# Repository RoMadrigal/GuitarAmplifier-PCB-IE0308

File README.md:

# GuitarAmplifier-PCB-IE0308

Repositorio para el proyecto final del curso IE0308 sobre el diseño de una PCB de un amplificador para guitarra. Contiene el circuito esquemático, el diseño de la PCB en *KiCad* y documentación sobre los componentes a utilizar, el procedimiento de diseño y otros detalles. 

Este repositorio y sus contenidos fueron diseñados durante el curso IE0308 durante el periodo I-2025 por los siguientes integrantes del equipo:

<div align="center">

|        **Integrantes**      | **Carné** | **Correo electrónico**|
|:---------------------------:|:---------:|:---------------------:|
|    Anthony Calvo García     |   C11433  |  anthonycalvo50@gmail.com |
|   Rodrigo Madrigal Montes   |   C24458  | rmadrigalmontes@gmail.com |

</div>

## Agradecimientos a PCBWay

Queremos expresar nuestro agradecimiento a **PCBWay** por su colaboración y apoyo en la fabricación de nuestras PCBs. La calidad de las placas recibidas, tanto en precisión de fabricación como en acabados, fue sobresaliente. Todo el proceso desde la carga de archivos hasta la recepción del paquete fue ágil, transparente y eficiente. 

Además siempre estuvieron disponibles para cualquier consulta, para asegurarse de que todo saliera según lo planeado, lo cual nos brindó mucho soporte y seguridad durante todo el proceso de pedido.

### PCB ensamblada

Una vez recibidas las placas de **PCBWay**, se procedió con el ensamblaje manual de todos los componentes. A continuación se muestran imágenes del resultado final:

<div align="center">

|  |
|:--:|
| *PCB ensamblada - sin los componentes externos conectados* |

</div>

<div align="center">

|  |
|:--:|
| *PCB ensamblada - con los componentes externos conectados* |

</div>

### Demostración de funcionamiento

A continuación, se presentan vídeos demostrativos del amplificador montado, funcionando correctamente tanto con una guitarra eléctrica como con un teléfono:

<p align="center">
  
  <br/>
  <em>Demostración del amplificador conectado a una guitarra eléctrica</em>
</p>

<p align="center">
  
  <br/>
  <em>Demostración del amplificador reproduciendo audio desde un teléfono</em>
</p>

Gracias a su servicio confiable y de altísima calidad, logramos ensamblar y probar con éxito nuestro amplificador, cumpliendo los objetivos del proyecto. Recomendamos sus servicios para estudiantes, profesionales y cualquier persona interesada en manufacturar PCBs de alta calidad. Más información en [pcbway.com](https://www.pcbway.com).

## Organización y contenido de los directorios 

Este repositorio contiene dos directorios principales, cuyos contenidos son:

- `kicad_project`: Contiene los archivos del esquemático, PCB y la configuarción del proyecto
    - `GuitarAmplifier.kicad_pcb`
    - `GuitarAmplifier.kicad_pro`
    - `GuitarAmplifier.kicad_sch`

- `outputs`: Contiene todos los archivos de salida de *KiCad*

Si se desea utilizar este diseño y manufacturarlo por medio de un fabricante se deben comprimir los archivos incluidos en la carpeta `outputs` en un archivo `.zip` y este se puede cargar en la página del fabricante para ordenar la fabricación de la PCB.

## Circuito base

El circuito completo del que partimos para diseñar la PCB fue primeramente fue armado y simulado en el simulador *Tina-TI*:

<div align="center">

|  |
|:--:|
| *Circuto completo del diseño* |

</div>

> [!NOTE]
> La documentación detallada de funcionamiento de cada etapa del circuito, elección de componentes, y consideraciones de diseño está disponible en la documentación adicional asociada al proyecto (ver `Wiki` de este repostitorio).

### Lista de componentes

A continuación se incluye una lista con los componentes utilizados en el diseño, con el mismo número que se les asignó en el diseño final de PCB:

<div align="center">

|   Componente   |   Valor / Modelo    |    Descripción    |
|:--------------:|:-------------------:|:-----------------:|
| R1 / R2   |     1 kΩ           |   Resistor de película metálica    |
| R3    |     1 MΩ           |   Resistor de película metálica     |
| R4    |     100 Ω           |   Resistor de película metálica     |
| R5    |     10 kΩ           |   Resistor de película metálica     |
| R6    |     3 kΩ           |   Resistor de película metálica     |
| R7 / R8    |     1.5 kΩ     |   Resistor de película metálica     |
| R9    |     3.3 kΩ           |   Resistor de película metálica     |
| R10    |     33 kΩ           |   Resistor de película metálica     |
| R11    |     170 Ω           |   Resistor de película metálica     |
| R12    |     10 Ω           |   Resistor de película metálica     |
| C1 / C3 / C11 / C15    |     470 nF          | Capacitor cerámico |
| C2 / C6 / C7 / C12   |     100 nF          | Capacitor de poliéster |
| C4 / C5 / C8 / C10 / C16   |     220 nF          | Capacitor de poliéster |
| C9    |     10 nF          | Capacitor de poliéster |
| C13    |     10 μF          | Capacitor electrolítico |
| C14    |     220 μF          | Capacitor electrolítico |
| U1 / U2   |     TL072CP      | Amplificador operacional |
| U3    |     LM386            | Amplificador de potencia |
| D1    |     1N4148            | Diodo rectificador |
| Gain / Low / Mid / High    |     50 kΩ            | Potenciómetro logarítmico |
| Volume    |     10 kΩ            | Potenciómetro logarítmico |
| J1    |     -         | Jack estéreo 6,3 mm |
| Battery / Speaker    |     -         | Terminal 01x02 5.08mm |
| Clean / O.D. Switch    |     -         | Terminal 01x03 5.08mm |

</div>

## Diseño de la PCB

Una vez definido el circuito final, se diseñó la PCB en *KiCad* con una arquitectura de **cuatro capas**:

- **F.Cu**: Ruta de señales
- **In1.Cu**: Plano de alimentación (+9V y +4.5V)
- **In2.Cu**: Plano de tierra (GND)
- **B.Cu**: Ruta de señales

### Capas de la PCB

<div align="center">

|  |
|:-----------------------------:|
|    *Capa superior (F.Cu)*     |

</div>

<div align="center">

|  |
|:-----------------------------:|
|    *Capa inferior (B.Cu)*     |

</div>

<div align="center">

|  |
|:-------------------------------------------:|
|      *Capa interna 1 - +9V / +4.5V*         |

</div>

<div align="center">

|  |
|:-------------------------------------:|
|        *Capa interna 2 - GND*         |

</div>

Además, se agregaron zonas de serigrafía, agujeros de montaje, así como textos identificativos y logotipos en el *silkscreen* con el nombre del proyecto y los autores. Como resultado final se muestra la PCB en el visor 3D de *KiCad* con y sin los modelos 3D 

<div align="center">

|  |
|:--:|
| *Vista 3D Frontal de la PCB en KiCad* |

</div>

<div align="center">

|  |
|:--:|
| *Vista 3D Trasera de la PCB en KiCad* |

</div>

<div align="center">

|  |
|:--:|
| *Vista 3D Frontal de la PCB en KiCad con modelos 3D* |

</div>

<div align="center">

|  |
|:--:|
| *Vista 3D Lateral Izquierda de la PCB en KiCad con modelos 3D* |

</div>

<div align="center">

|  |
|:--:|
| *Vista 3D Lateral Derecha de la PCB en KiCad con modelos 3D* |

</div>

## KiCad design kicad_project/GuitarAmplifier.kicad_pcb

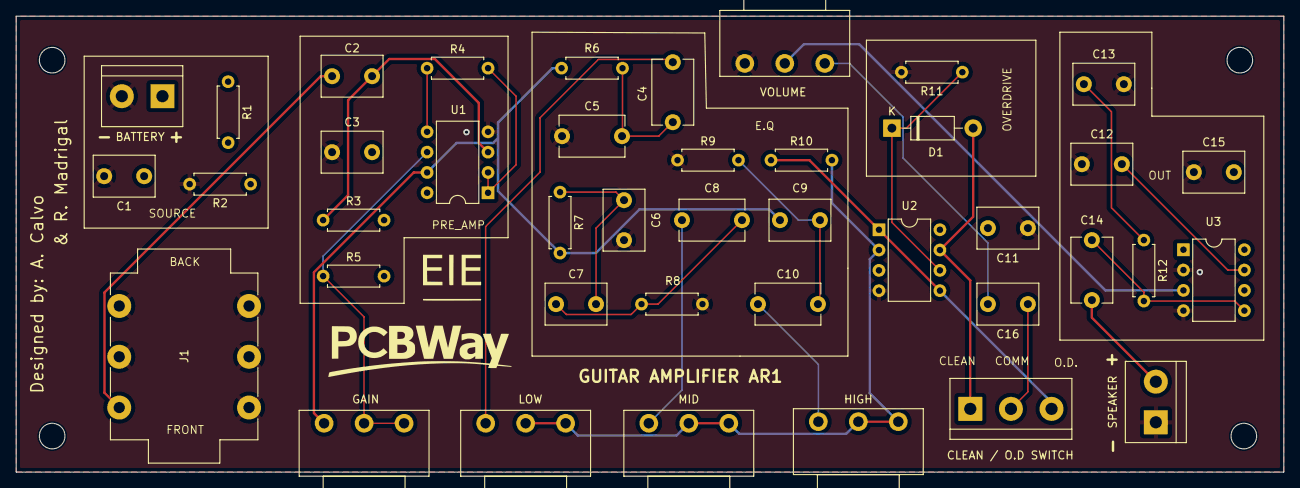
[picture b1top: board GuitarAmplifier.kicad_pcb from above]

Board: 4 copper layers, 158.5 x 57.0 mm, 45 parts (0 on the bottom side), 27 nets.

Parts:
BATTERY: Screw_Terminal_01x02; TerminalBlock_bornier-2_P5.08mm
C1, C3, C11, C12, C13, C15, C16: 10u; C_Disc_D7.5mm_W5.0mm_P5.00mm
C2, C9: 10n; C_Disc_D7.5mm_W5.0mm_P5.00mm
C4, C5, C8, C10: 220n; C_Disc_D8.0mm_W5.0mm_P7.50mm
C6, C7: 100n; C_Disc_D7.5mm_W5.0mm_P5.00mm
C14: 220u; C_Disc_D8.0mm_W5.0mm_P7.50mm
CLEAN / O.D SWITCH: Terminal_01x03; TerminalBlock_bornier-3_P5.08mm
D1: 1N4002; D_DO-41_SOD81_P10.16mm_Horizontal
GAIN: 50k; Potentiometer_Piher_PC-16_Single_Horizontal
H1, H2, H3, H4: MountingHole_3.2mm_M3
HIGH: 50k; Potentiometer_Piher_PC-16_Single_Horizontal
J1: NMJ6HCD2; Jack_6.35mm_Neutrik_NMJ6HCD2_Horizontal
LOW: 50k; Potentiometer_Piher_PC-16_Single_Horizontal
MID: 50k; Potentiometer_Piher_PC-16_Single_Horizontal
R1, R2, R5: 10k; R_Axial_DIN0207_L6.3mm_D2.5mm_P7.62mm_Horizontal
R3: 1MEG; R_Axial_DIN0207_L6.3mm_D2.5mm_P7.62mm_Horizontal
R4: 100; R_Axial_DIN0207_L6.3mm_D2.5mm_P7.62mm_Horizontal
R6: 3k; R_Axial_DIN0207_L6.3mm_D2.5mm_P7.62mm_Horizontal
R7, R8: 1.5k; R_Axial_DIN0207_L6.3mm_D2.5mm_P7.62mm_Horizontal
R9: 3.3k; R_Axial_DIN0207_L6.3mm_D2.5mm_P7.62mm_Horizontal
R10: 33k; R_Axial_DIN0207_L6.3mm_D2.5mm_P7.62mm_Horizontal
R11: 175; R_Axial_DIN0207_L6.3mm_D2.5mm_P7.62mm_Horizontal
R12: 10; R_Axial_DIN0207_L6.3mm_D2.5mm_P7.62mm_Horizontal
SPEAKER: Screw_Terminal_01x02; TerminalBlock_bornier-2_P5.08mm
U1, U2: TL072CP; DIP-8_W7.62mm
U3: LM386; DIP-8_W7.62mm
VOLUME: 50k; Potentiometer_Piher_PC-16_Single_Horizontal

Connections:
+4.5V: C1.1, R1.2, R2.1, R3.2, R5.2, U2.3 (1IN+)
+9V: BATTERY.1, C3.2, C11.2, C15.2, R1.1, U1.8 (VCC+), U2.8 (VCC+), U3.6 (V+)
/OUT_Clean: CLEAN / O.D SWITCH.3, R10.1, U2.1 (1OUT), U2.5 (2IN+)
/OUT_Eq: HIGH.2, HIGH.3, LOW.2, LOW.3, MID.2, MID.3, R10.2, U2.2 (1IN-)
/OUT_OverD: CLEAN / O.D SWITCH.1, D1.2 (A), U2.7 (2OUT)
/OUT_PreAmp: C9.2, GAIN.1, R6.2, R7.2, U1.7 (2OUT)
/System_Out: C14.2, SPEAKER.2
GND: BATTERY.2, C1.2, C3.1, C5.1, C6.1, C11.1, C12.1, C13.2, C15.1, J1.R, J1.RN, J1.S, J1.SN, J1.TN, R2.2, R8.1, R9.1, R11.2, SPEAKER.1, U1.4 (VCC-), U2.4 (VCC-), U3.2 (-), U3.4 (GND), VOLUME.3
unnamed: C2.2, J1.T
unnamed: C4.1, LOW.1
unnamed: C4.2, C5.2, R6.1
unnamed: C6.2, C7.2, R7.1
unnamed: C7.1, C8.2, R8.2
unnamed: C8.1, MID.1
unnamed: C10.1, HIGH.1
unnamed: C9.1, C10.2, R9.2
unnamed: C13.1, R12.1
unnamed: C14.1, R12.2, U3.5
unnamed: C16.2, VOLUME.1
unnamed: D1.1 (K), R11.1, U2.6 (2IN-)
unnamed: C16.1, CLEAN / O.D SWITCH.2
unnamed: C2.1, R3.1, U1.3 (1IN+)
unnamed: R4.2, U1.1 (1OUT), U1.2 (1IN-)
unnamed: R4.1, U1.5 (2IN+)
unnamed: GAIN.2, GAIN.3, R5.1, U1.6 (2IN-)
unnamed: U3.3 (+), VOLUME.2
unnamed: C12.2, U3.7 (BYPASS)

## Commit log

2025-06-07 Agregando tipos de archivos adicionales al .gitignore
2025-06-07 Agregando imagen del circuito final en el directorio images
2025-06-13 Se agregan las etapas de alimentacion, buffer y pre-amp
2025-06-13 Agregando etapa de ecualizacion
2025-06-14 Agregando informacion de contacto y sobre el circuito base en el README.md
2025-06-14 Agregando nota de la documentacion detallada en el README.md
2025-06-15 Agregando el overdrive, la etapa de salida ambas verificadas y una representación casi finalizada de la PCB
2025-06-15 Realizando acomodo final en el esquematico y PCB
2025-06-15 Definiendo las capas de alimentacion y tierra en la PCB
2025-06-16 Conectando pistas y vias en la capa superior de la PCB
2025-06-16 Agregando el enrutamiento final y una reconfiguración de la placa
2025-06-16 Terminando de rellenar la capa inferior y ajustando las huellas de los conectores
2025-06-16 Agregando detalles finales en la serigrafia de la PCB
2025-06-16 Reasignando huella de los potenciometros
2025-06-16 Agregando logotipos y verificando la configuracion final
2025-06-17 Agregando carpeta outputs con los archivos gerber y .drl
2025-06-25 Update README.md
    agregando correo electronico.
2025-07-05 Agregando secciones de diseño y agradecimiento a PCBWay en el README.md
2025-07-05 Modificando ubicación de las imagenes de la PCB en el README.md
2025-07-05 Agregando lista de componentes y corrigiendo errores en el README.md
2025-07-05 Agregando seccion de videos demostrativos al README.md
2025-07-06 Agregando imagenes del resultado final y disenyo en Kicad al README.md
2025-07-06 Agregando las imagenes del README.md en el directorio images
2025-07-06 Agregando enlaces a videos demostrativos del funcionamiento en el README.md
2025-07-06 Agregando tabla de componentes en el README.md
2025-07-06 Corrigiendo detalles finales en el README.md
2025-08-08 Actualizando documentacion
2025-08-08 Agregando serigrafia trasera
2025-08-08 Agregando foto de la vista trasera
2025-08-08 Agregando foto de la vista trasera al README
2025-09-25 Agregando imagenes con modelos 3D en el README.md
2025-09-25 Agregando cambio en conector de switch y modelos 3D de componentes faltantes
2025-09-25 Agregando archivos actualizados de fabricacion
2025-10-07 Agregando dibujo del capibara
2025-10-07 Se corrigio la Vista3DInferior
2025-10-07 Corrigiendo imagen de la vista3DInferior
2025-12-07 Corrigiendo un error en la seccion: Organizacion y contenido de los directorios
